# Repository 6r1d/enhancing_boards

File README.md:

# Enhancing boards

Hello! This is a place I will be pushing KiCad boards and documentation for those.
I am doing that to be able to show, discuss and improve those boards, also I want them to be useful for someone.

There are lots of ready boards for DIY enthusiasts, but I can't always find a well-tested layout made in open-source software, so there's always something to improve, too. :-)

## Plans
I am interested in electronic music synthesizers and single-board computers that can be used in those; I intend to test different microcontrollers and sound-related hardware. Besides that, I have a ton of breakout boards from China. I want reusable layouts for chips, so that's something I'll gradually clean up and add here, too.

Currently I'm waiting for a very primitive [ESP32-Wroom](https://www.espressif.com/sites/default/files/documentation/esp32-wroom-32_datasheet_en.pdf) boards to determine if 3.3V power is a minimal requirement.
If that's the case, I will add my own [ESP32](https://www.espressif.com/en/products/socs/esp32) board here.

### Interesting ICs
There are integrated circuits I really want to use later.

* [STM32F103C8T6](https://www.st.com/resource/en/datasheet/stm32f103c8.pdf) microcontroller, because Maple and Blue Pill were very nice until the clone boards with clone chips started popping up. New ones are really hard to distinguish visually!
* [Azoteq IQS263B](https://www.azoteq.com/product/iqs263b/) capacitive sensor IC, I²C interface. Allows to make capacitive wheels, sliders and buttons.
* [Azoteq IQS550-B000](https://www.azoteq.com/product/iqs550-b000/) capacitive sensor IC, 15 rows, 10 columns, 3584 x 2304 max resolution, I²C interface. Allows to make large capacitive sensor panels. **UPD**: I ordered the test kit from DigiKey and it is being delivered by USPS to Qwintry warehouse right now.
* [CAP1188](https://www.microchip.com/wwwproducts/en/CAP1188) capacitive sensor IC, 8 capacitive sensor inputs, I²C interface.
* [TXS0108E](https://www.ti.com/lit/ds/symlink/txs0108e.pdf) / YF08E and maybe other level converters, since I have those. (There is some concern about the fakes, too, because I saw very different labels for the same chip.)
* [SI4735](https://www.silabs.com/documents/public/data-sheets/Si4730-31-34-35-D60.pdf), radio receiver IC because it is tiny, works, and might be interesting to play with.

## Testing

When I can, I will test the boards using the toner-transfer method, adding a note about the results and fixing the boards. Otherwise, I'll order everything I can't make elsewhere.

If you want to do tests right now, **feel free to create an issue**! I will provide any additional info you'll want for toner-transfer method or I will help with factory Gerber.

## Current boards

| Directory                             | State                            | Description                                         |
| ------------------------------------- | -------------------------------- | --------------------------------------------------- |
| [PCM5102A](/PCM5102A)                 | UNTESTED                         | [PCM5102A](https://www.ti.com/product/PCM5102A) [I²S](https://en.wikipedia.org/wiki/I%C2%B2S) dac with [TPA6132A2](https://www.ti.com/product/TPA6132A2) headphone amp |
| [MIDI I/O](/MIDI_IO)                  | STABLE, tested for 5V | [MIDI](https://en.wikipedia.org/wiki/MIDI) [I/O](https://en.wikipedia.org/wiki/Input/output) board for 5V devices                       |
| [MCP4725 breakout](/MCP4725_breakout) | UNTESTED                         | [I²C](https://en.wikipedia.org/wiki/I%C2%B2C) [DAC](https://en.wikipedia.org/wiki/Digital-to-analog_converter) breakout board, 1 output                    |
| [MCP4728 breakout](/MCP4728_breakout) | UNTESTED                         | [I²C](https://en.wikipedia.org/wiki/I%C2%B2C) [DAC](https://en.wikipedia.org/wiki/Digital-to-analog_converter) breakout board, 4 outputs                   |
| [MUX_4067](/MUX_4067)                 | UNTESTED                         | 16-pin analog / digital [multiplexor](https://en.wikipedia.org/wiki/Multiplexer) breakout board  |

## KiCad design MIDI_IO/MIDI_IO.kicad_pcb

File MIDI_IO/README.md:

# MIDI I/O board

Assembled:

3D render:

[PCB photos](https://i.imgur.com/VaKc3Vo.jpg)

## Current state

I have five physical boards and each of those is working. Moreover, long-term tests are done.
I'm still concerned about the device speed and I want to perform 24 hour long tests on 5V and 3.3V devices, as well.

## Specifications

This board has two DIN-5 ports for input and output and [6N138](https://www.vishay.com/docs/83605/6n139.pdf) to isolate input signal. 6N138 optoisolators were bought [here](https://aliexpress.ru/item/32545548201.html?spm=a2g0s.9042311.0.0.264d33edC1LcYz) and were tested by me well.
I've bought my DIN-5 sockets [here](https://aliexpress.ru/item/32402564814.html) on AliExpress, which seems cheap enough.

It is inspired by the fact [AliExpress](http://aliexpress.com/) boards for [MIDI](https://en.wikipedia.org/wiki/MIDI) are not that good and I had to [solder a resistor](https://twitter.com/I_am_6r1d/status/1299311510662021120) straight onto the optocouple leads to make one work.

It uses `1k 100 mHz` [ferrite beads](https://article.murata.com/en-eu/article/basics-of-noise-countermeasures-lesson-4) for [EMI protection](https://en.wikipedia.org/wiki/Electromagnetic_interference), currently [ILBB-0603ER102V](https://static6.arrow.com/aropdfconversion/c4f424f1ec3f9ac2c3a4ec0c3df1e3ee2574f7a5/ilbb0603.pdf) by [Vishay](https://www.vishay.com/).

This board is designed in [KiCad 5.1.6](https://kicad-pcb.org/).
Issues and advices are welcome!

## Testing

I was concerned about the components overheating over a long-term use,
so I decided to "spam" a hardware synthesizer with MIDI messages to check how it behaves.

First test was relatively simple: random notes were sent to Casio Privia synthesizer on low volume for three hours when input voltage was 5v.
I did not notice any glitches in the process (no randomly changing instruments or velocity).
To perform the test, I have used Arduino Uno and Arduino Mega boards.

Then I did a similar test for ~15 minutes on STM32 board (Blue Pill) and ESP32-WROOM board, both sent 3.3 V input to the board.

I also monitored how the signal is received by checking available bytes on UART. I should do more extensive tests later.
I am mostly interested in sending lots of MIDI data from E-MU 0404 to a 3.3V device to understand how well it behaves.

## Components

### 5V mode

This board is initially intended for use with devices, which have 5V [logic level](https://en.wikipedia.org/wiki/Logic_level) like [Arduino](https://www.arduino.cc/)
and 3.3 V board should be different component-wise, not layout-wise.

Schematic contains correct and tested resistor values for 5V,
according to MIDI DIN electrical [specification](https://www.midi.org/specifications-old/item/midi-din-electrical-specification).

This specification doesn't clearly state a resistor value for 6n138 optoisolator, currently it is 220 Ω,
which works for hours in practice, but **should be optimized** later.
The resistor I'm speaking of is called `R4` on KiCad schematic. In MIDI DIN spec it's called `Rd`.
It influences `speed of bit switching` on the optoisolator side connected to `RX` pin and `the power consumption`.

### 3.3 V mode

I have sent and received data on both STM32 and ESP32 using the current design.
`R4` value was the same as in 5V version, i.e. 220 Ω, which might be too low for the task.
While it gives a high switching speed (apparently, I don't have an oscilloscope to check right now),
it is different from the recommended value range, too.

Further tests should adress that and I should test the board with more appropriate resistors.

There are many possible changes to make for 3.3V. Some require changing the layout, some don't.

 * [PJRC](http://web.archive.org/web/20201025215735/https://forum.pjrc.com/threads/45416-Base-Emitter-Resistor-for-6N139-on-MIDI-input) - physics of the process, fixes, 6n137 recommendation
 * [EE StackExchange](https://electronics.stackexchange.com/questions/165255/midi-in-many-circuits) - more on physics, TLP2361 and H11L1 recommendation, possible layout alteration
 * [Samplerbox](https://www.samplerbox.org/article/midiinwithrpi) - recommendations about Raspberry Pi usage, a combination of `R4` = 1k and `R5` = 10k. Comment tells it doesn't work, though.
 * [EE StackExchange](https://electronics.stackexchange.com/questions/288448/minimize-current-consulption-for-midi-input-circuit) topic about power consumption recommends another topology, clamping the output transistor with Schottky diode like `SD101`, `BAS70`, `RB751`
 * [EE StackExchange](https://electronics.stackexchange.com/questions/102884/how-to-calculate-exactly-resistors-values-of-opto-coupler) also has a topic on exact calculation for a pull-up resistor

The **simplest** would be to pick `R4` = 1k, `R5` = 10k and perform the tests between two boards.
"MIDI in many circuits" topic explains that R5 range should be between 4.7 kΩ and 10 kΩ.

## To-Do

- [x] Check contacts on physical DIN-5 sockets: both pins and sizes
- - **UPD**: sockets have arrived, testing soon
- - **UPD-2**: ordered the board, optocouples and diodes arrived, waiting for passive components
- [x] Finish compatibility with current [MIDI DIN electrical specification](https://www.midi.org/specifications/item/midi-din-electrical-specification)
- [x] Clean components up
- [x] Order a PCB
- [x] Assemble a PCB
- [x] Test 3V3 mode on STM32 with available resistors
- [x] Test 3V3 mode on ESP32-WROOM with available resistors
- [ ] Run a high-speed byte transfer through an optocouple and compare sent and received byte for a day
- [ ] Test connection reliability between two 3V3 devices both usin MIDI I/O board
- [ ] Test 3V3 mode for [Raspberry Pi](https://www.raspberrypi.org/), add a level shifter if it will be required. Look at [this article](https://openenergymonitor.org/forum-archive/node/12412.html) if things start to break.

## Credits

* [KiCad](https://kicad-pcb.org/) 3d Packages and library by Walter Lain (`kcswalter` at `member.fsf.org`), downloaded at [Smisioto.No-IP.org](http://smisioto.no-ip.org/elettronica/kicad/kicad-en.htm)

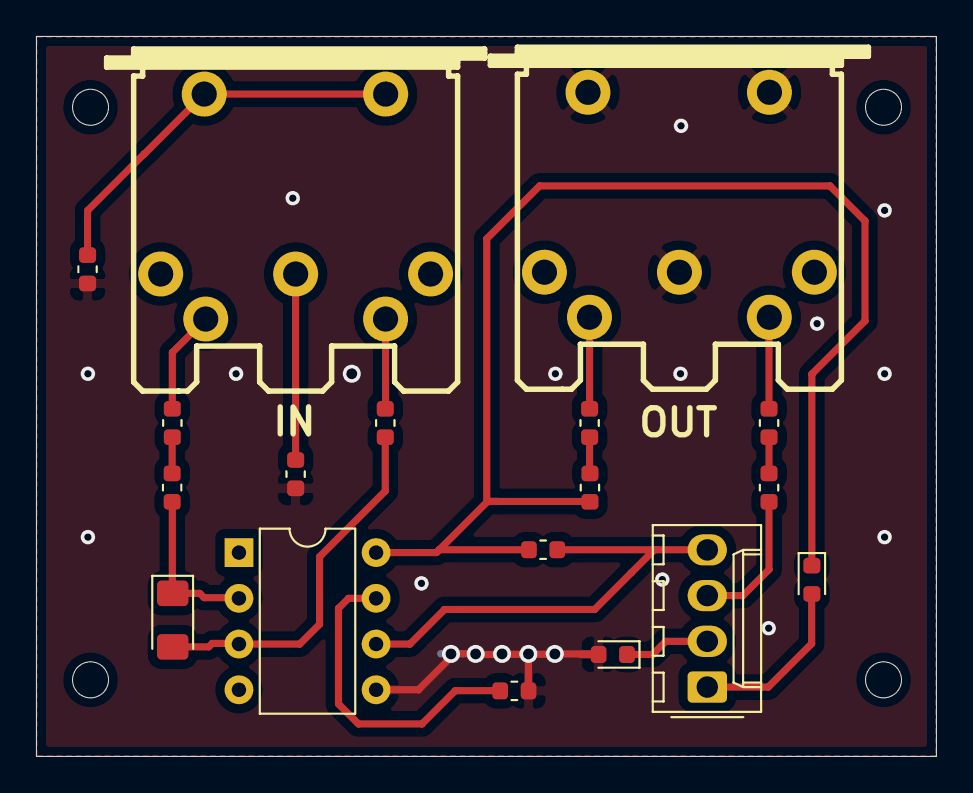
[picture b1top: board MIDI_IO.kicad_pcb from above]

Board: 2 copper layers, 50.0 x 40.0 mm, 23 parts (1 on the bottom side), 18 nets.

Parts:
C1, C2: 0.1uF; C_0603_1608Metric
D1: 1N914; D_1206_3216Metric_Pad1.42x1.75mm_HandSolder
D2, D3: D; D_0603_1608Metric
FB1, FB2, FB3, FB4: 1k 100mHz; L_0603_1608Metric
H1, H2, H3, H4: MountingHole_Pad; MountingHole_2mm
J1: Conn_01x04; Molex_KK-254_AE-6410-04A_1x04_P2.54mm_Vertical
J_IN_1: DIN-5_180degree_JS; din-5-shielded
J_OUT_1: DIN-5_180degree_JS; din-5-shielded
R1, R2, R3, R4: 220; R_0603_1608Metric
R5: 4.7k; R_0603_1608Metric
U1: 6N138; DIP-8_W7.62mm
svg2mod: G***; Grid_logo

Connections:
+5V: D2.1, R2.1, R4.1, U1.8
GND: C1.2, C2.2, D3.2, J_OUT_1.2, J_OUT_1.6, R5.2, U1.5
IN_SH: C1.1, J_IN_1.2
IN_SH_OUT: C2.1, J_IN_1.6
unnamed: D1.1, R3.1, U1.2
unnamed: D1.2, FB4.1, U1.3
unnamed: D2.2, J1.1
unnamed: D3.1, J1.2
unnamed: FB1.1, J_OUT_1.5
unnamed: FB1.2, R1.1
unnamed: FB2.1, R2.2
unnamed: FB2.2, J_OUT_1.4
unnamed: FB3.1, R3.2
unnamed: FB3.2, J_IN_1.4
unnamed: FB4.2, J_IN_1.5
unnamed: R5.1, U1.7
RX: J1.4, R4.2, U1.6
TX: J1.3, R1.2

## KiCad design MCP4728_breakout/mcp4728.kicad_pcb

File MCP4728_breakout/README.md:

# MCP4728 breakout board

## Idea

This breakout board has 4 DAC ports, controlled by I²C protocol. It is based on the default schematic from `MCP4728` datasheet and Adafruit breakout board.

**Attention!** Output voltage will depend on the input! To imagine how that works, let's say you have a 5V source. Integer you are sending using I²C varies from 0 to 4095. Now, when you have 5V input and 4095 on I²C, you'll have 5V on the output. If you set 0 on I²C, you'll get zero voltage. But you can put any value between 0 and 4095, too, getting all possible in-between voltages. Same goes for 3.3V.

It is currently untested, but the board seems simple enough so there should be no errors.

## Documents

[Datasheet](https://ww1.microchip.com/downloads/en/DeviceDoc/22187E.pdf)

## Links

* [Adafruit breakout board](https://learn.adafruit.com/adafruit-mcp4728-i2c-quad-dac/downloads) documentation

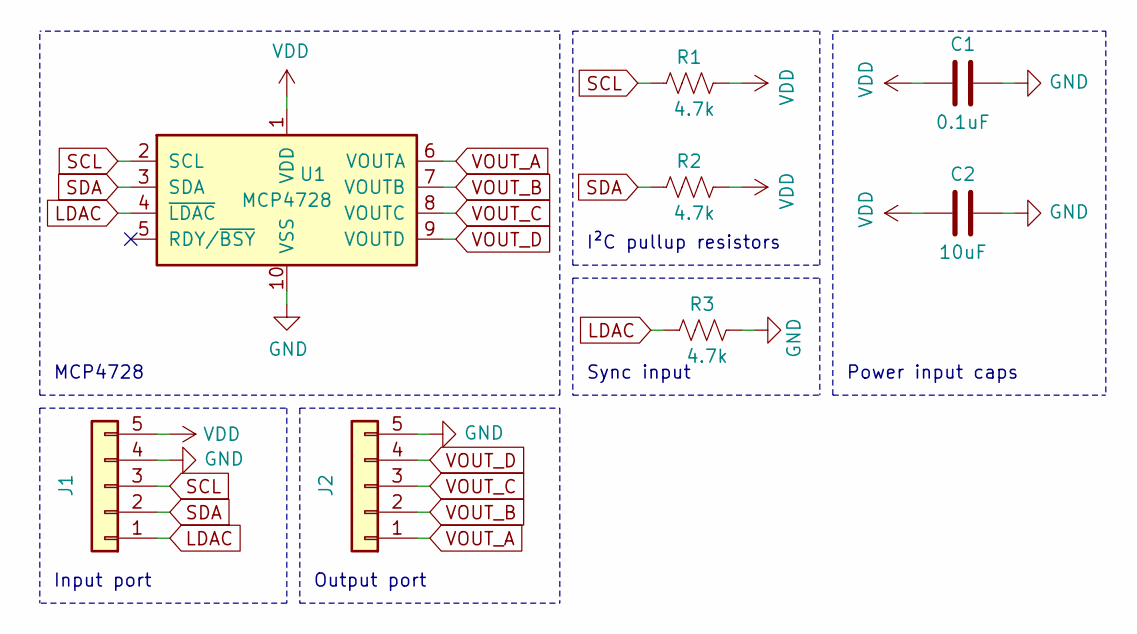
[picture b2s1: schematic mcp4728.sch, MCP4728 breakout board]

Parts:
C1: 0.1uF; C_0603_1608Metric
C2: 10uF; C_0603_1608Metric
J1, J2: Conn_01x05; PinHeader_1x05_P2.54mm_Vertical
R1, R2, R3: 4.7k; R_0603_1608Metric
U1: MCP4728; MSOP-10_3x3mm_P0.5mm

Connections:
GND: C1.1, C2.1, J1.4, J2.5, R3.2, U1.10 (VSS)
LDAC: J1.1, R3.1, U1.4 (~LDAC)
SCL: J1.3, R1.1, U1.2 (SCL)
SDA: J1.2, R2.1, U1.3 (SDA)
VDD: C1.2, C2.2, J1.5, R1.2, R2.2, U1.1 (VDD)
VOUT_A: J2.1, U1.6 (VOUTA)
VOUT_B: J2.2, U1.7 (VOUTB)
VOUT_C: J2.3, U1.8 (VOUTC)
VOUT_D: J2.4, U1.9 (VOUTD)

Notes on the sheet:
MCP4728
I²C pullup resistors
Input port
Output port
Power input caps
Sync input

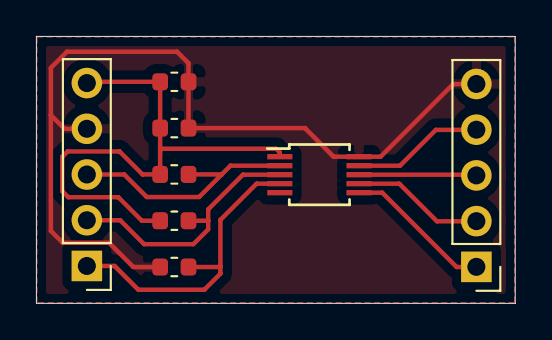
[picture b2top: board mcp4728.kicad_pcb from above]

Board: 2 copper layers, 26.6 x 14.8 mm, 8 parts (0 on the bottom side), 9 nets.

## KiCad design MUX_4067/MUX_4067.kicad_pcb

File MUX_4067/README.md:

# 16-pin analog / digital multiplexor breakout board

## Idea

If you have never used multiplexors, this IC connects a single pin to **one of** the several outputs, where an output pin is picked using **other** digital input pins. Think [railroad switch](https://en.wikipedia.org/wiki/Railroad_switch), but for electronics, not for railroad.

I had some of those mux board around for quite some time and they are working nicely with Arduino, so I decided to make a copy of a very short schematic and to make my own layout. Why? Well, as usual, to test and be sure I can use them in my own devices later.

## Documentation

[Datasheet](https://www.ti.com/lit/ds/symlink/cd74hc4067.pdf)

## To-Do

- [ ] Use a multimeter's continuity testing on the original to ensure I'm using correct pins
- [ ] Order a board prototype
- [ ] Do a bunch of tests to determine it's not worse than normal breakout boards
- [ ] Create a 8-pin layout

## Links

* [SparkFun breakout board](http://cdn.sparkfun.com/datasheets/BreakoutBoards/Analog-Digital-Mux-Breakout-v11.pdf)
* [Arduino code for interacting with Mux](https://www.codrey.com/arduino-projects/analog-multiplexer-demultiplexer-primer/)

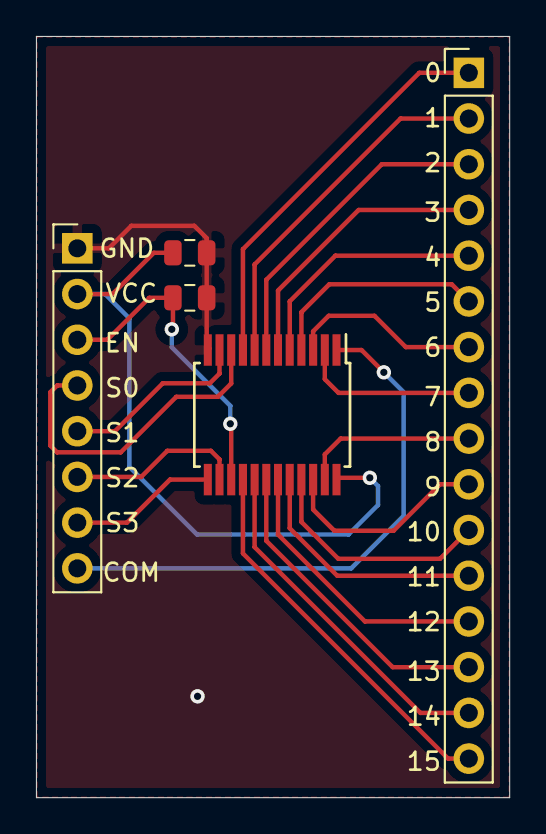
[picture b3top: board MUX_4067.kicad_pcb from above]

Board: 2 copper layers, 26.3 x 42.3 mm, 5 parts (0 on the bottom side), 24 nets.

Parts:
C1: 0.1uF; C_0805_2012Metric
J1: Conn_01x08; PinHeader_1x08_P2.54mm_Vertical
J2: Conn_01x16; PinHeader_1x16_P2.54mm_Vertical
R1: 10k; R_0805_2012Metric
U1: CD74HC4067SM; SSOP-24_5.3x8.2mm_P0.65mm

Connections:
COM: J1.8, U1.1
EN: J1.3, R1.1, U1.15
GND: C1.2, J1.1, R1.2, U1.12
unnamed: J2.1, U1.9
unnamed: J2.2, U1.8
unnamed: J2.3, U1.7
unnamed: J2.4, U1.6
unnamed: J2.5, U1.5
unnamed: J2.6, U1.4
unnamed: J2.7, U1.3
unnamed: J2.8, U1.2
unnamed: J2.9, U1.23
unnamed: J2.10, U1.22
unnamed: J2.11, U1.21
unnamed: J2.12, U1.20
unnamed: J2.13, U1.19
unnamed: J2.14, U1.18
unnamed: J2.15, U1.17
unnamed: J2.16, U1.16
S0: J1.4, U1.10
S1: J1.5, U1.11
S2: J1.6, U1.14
S3: J1.7, U1.13
VCC: C1.1, J1.2, U1.24

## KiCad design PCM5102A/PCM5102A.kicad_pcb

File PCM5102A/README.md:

# PCM 5102A interface for Raspberry PI

This board essentially consists of a [PCM5102A DAC](https://www.ti.com/lit/ds/symlink/pcm5102a.pdf) and [TPA6132A2 amplifier](https://www.ti.com/lit/ds/symlink/tpa6132a2.pdf) ICs.

[PCM5102A](https://www.ti.com/lit/ds/symlink/pcm5102a.pdf) IC is used in [PLL operation](https://en.wikipedia.org/wiki/Phase-locked_loop) schematic.
It means [SCK pin](https://hackaday.com/2019/04/18/all-you-need-to-know-about-i2s/) is not used and frequency generation happens internally, using phase-locked loop control system.
According to the datasheed, this configuration is not in any way bad and even slightly reduces [electromagnetic interference](https://en.wikipedia.org/wiki/Electromagnetic_interference).
I am using PCM5102A because it has high sound quality and mute circuitry.
Also, I ordered a board with this chip to test with Raspberry Pi before starting my own one.

I added [TPA6132A2](https://www.ti.com/lit/ds/symlink/tpa6132a2.pdf) headphone amplifier to isolate DAC from other devices.
It is used in a single-ended input signal mode. I have concerns about damaging the DAC with short circuit, so that's why there's a tiny amplifier IC.

Current 2-ldo schematic is inspired by ["GY" board from AliExpress](https://i.stack.imgur.com/ZBK8Q.jpg).
I got a working one at [WavGat store](https://aliexpress.ru/item/33001714060.html).

There are also 3-ldo versions of the same schematic by AiDiy.cc.
I guess it has a separate digital, analog and charge pump LDO, and it's a well-known [AMS-1117-3.3](http://www.advanced-monolithic.com/pdf/ds1117.pdf), at that!
It will be nice to test if there is any difference in sound later.

This board is designed in [KiCad 5.1.6](https://kicad-pcb.org/). It has 5V input voltage and 3.3V I²S voltage. Issues and advices are welcome!

## Progress

* I checked schematic using two datasheets paying as much attention as I can. It is still possible to encounter some issues and I haven't tested the board design yet.
* I found out my `5V` label is not related to the signal. RaspberryPi signal level is 3.3V. Changes are not required, since board is based on a design, tested with RaspberryPi.

## To-Do

- [ ] Do a [toner-transfer method](https://hackaday.com/2016/09/12/take-your-pcbs-from-good-to-great-toner-transfer/) test
- [ ] Test with [jumpers](https://en.wikipedia.org/wiki/Jumper_(computing))
- [ ] Remove excess power wiring from the layout
- [ ] Do a second toner-transfer method test board
- [ ] Add labels on the board to mark inputs and outputs
- [ ] Order a test batch at [PCBWay](https://www.pcbway.com/) / [JLCPCB](http://jlcpcb.com/) / etc.
- [ ] Add labels after the best board layout is established
- [ ] It will be nice to have optocouples to control the DAC and AMP mute circuitry after the prototype is working. (Analyze ChipDip mute circuit below)
- [ ] It will be interesting to test 1 and 3 LDO configuration later. It seems the datasheet relies on one LDO, while AiDiy schematic relies on three.
- [ ] Add a MUTE pin controlling optocouples for DAC and AMP ICs

UPD: TPA6132 breakout board is here, so I can test it before I do toner-transfer. Sep 10, 2020.

## Datasheets

* [DAC datasheet](https://www.ti.com/lit/ds/symlink/pcm5102a.pdf)
* [AMP datasheet](https://www.ti.com/lit/ds/symlink/tpa6132a2.pdf)

## Other links

* [StackOverflow](https://raspberrypi.stackexchange.com/questions/76188/how-to-make-pcm5102-dac-work-on-raspberry-pi-zerow) question inspiring me to use the initial board
* [Player.ru](http://player.ru/showthread.php?t=188998&page=207) - Hi-Res chinese board photos by maxkur, jumper pads configuration info (page 207)
* [Goldilocks Analogue schematic](https://feilipu.files.wordpress.com/2014/04/goldilocksanaloguedacamplifiers.png), which inspired me to use TPA6132A2 amp.
* [ChipDip.ru circuit](https://static.chipdip.ru/lib/335/DOC004335833.pdf) has an interesting XSMT connection for debouncing mute signal

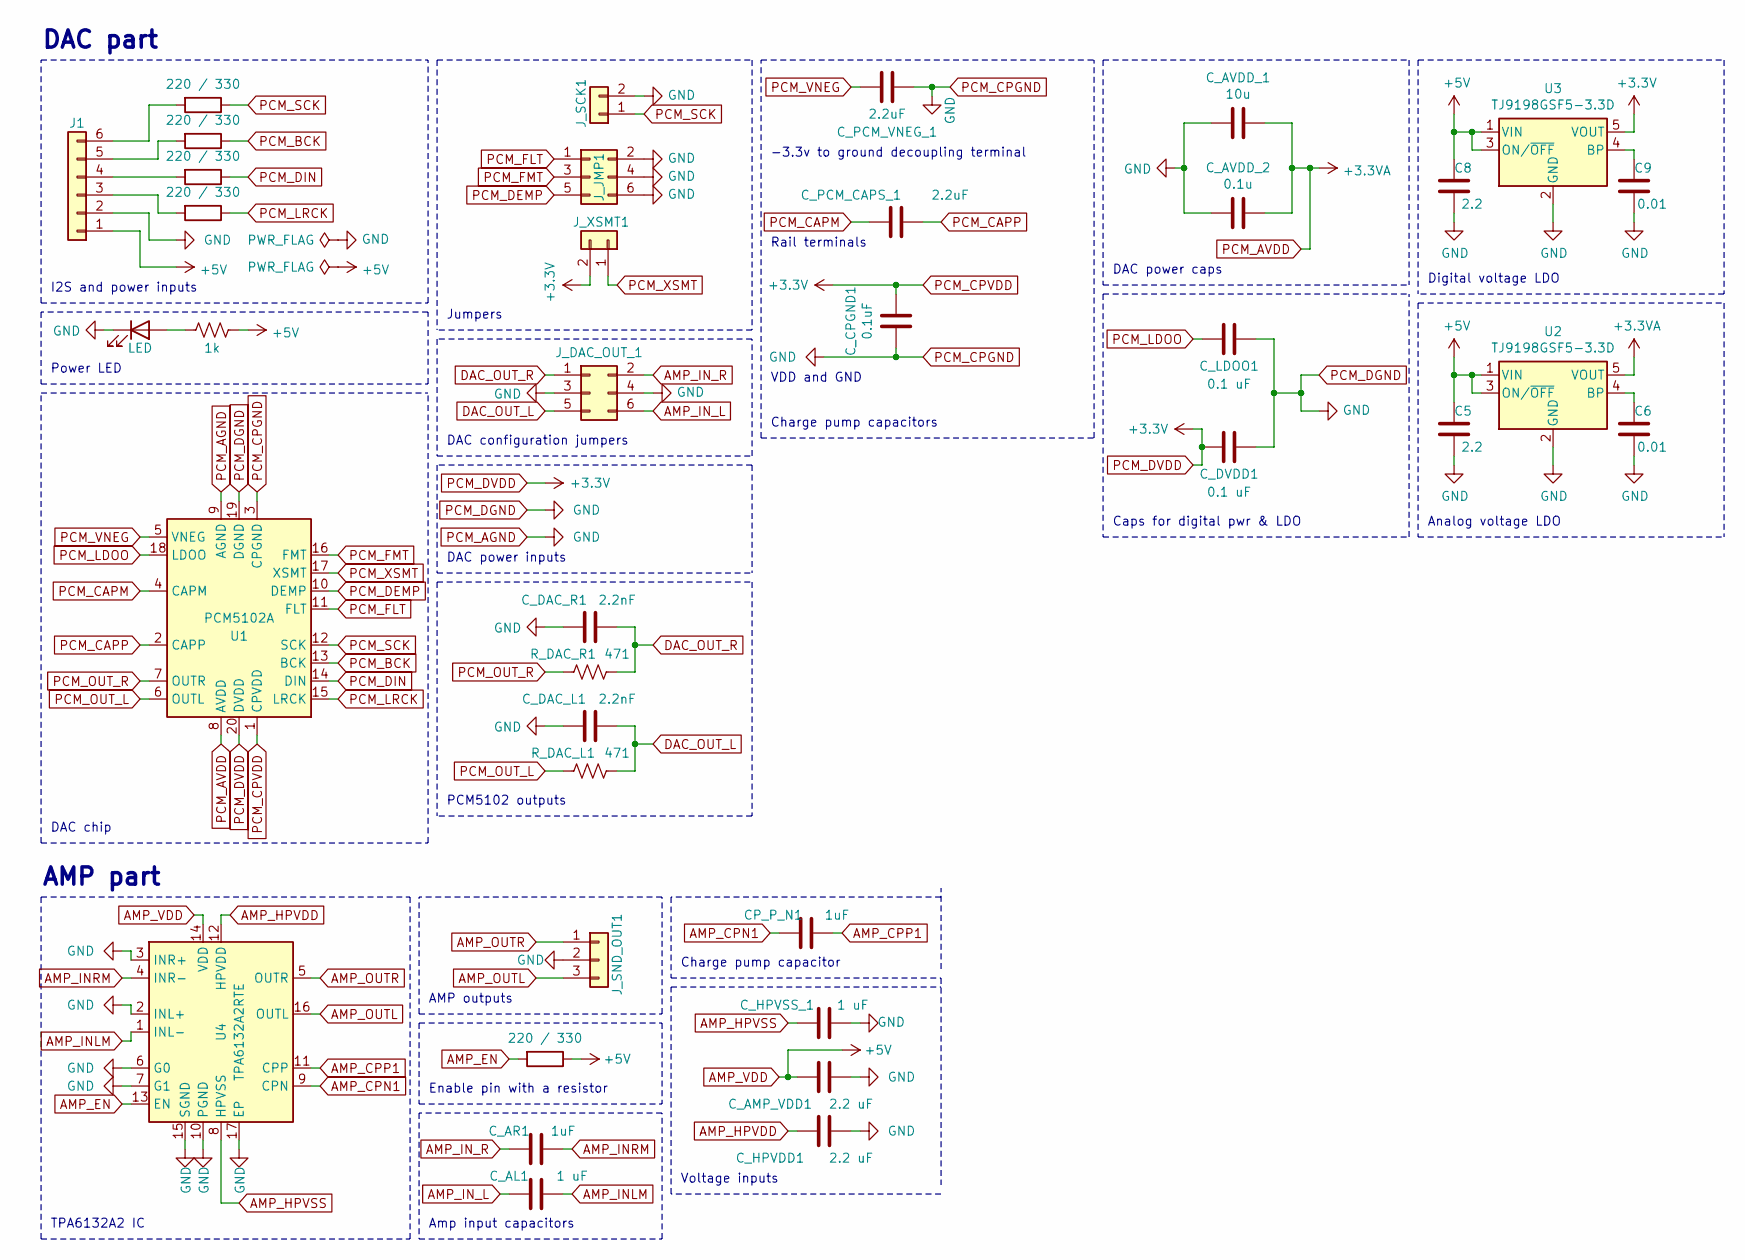
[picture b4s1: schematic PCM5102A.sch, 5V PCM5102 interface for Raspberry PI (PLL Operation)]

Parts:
C5, C8: 2.2; C_0603_1608Metric
C6, C9: 0.01; C_0603_1608Metric
CP_P_N1: 1uF; C_0603_1608Metric
C_AL1: 1 uF; C_0603_1608Metric
C_AMP_VDD1: 2.2 uF; C_0603_1608Metric
C_AR1: 1uF; C_0603_1608Metric
C_AVDD_1: 10u; C_0603_1608Metric
C_AVDD_2: 0.1u; C_0603_1608Metric
C_CPGND1: 0.1uF; C_0603_1608Metric
C_DAC_L1: 2.2nF; C_0603_1608Metric
C_DAC_R1: 2.2nF; C_0603_1608Metric
C_DVDD1: 0.1 uF; C_0603_1608Metric
C_HPVDD1: 2.2 uF; C_0603_1608Metric
C_HPVSS_1: 1 uF; C_0603_1608Metric
C_LDOO1: 0.1 uF; C_0603_1608Metric
C_PCM_CAPS_1: 2.2uF; C_0603_1608Metric
C_PCM_VNEG_1: 2.2uF; C_0603_1608Metric
D1: LED; LED_0603_1608Metric_Castellated
J1: Conn_01x06; PinHeader_1x06_P2.54mm_Vertical
J_DAC_OUT_1: Conn_02x03_Odd_Even; PinHeader_2x03_P2.54mm_Vertical
J_JMP1: Conn_02x03_Odd_Even; PinHeader_2x03_P2.54mm_Vertical
J_SCK1: Conn_01x02; PinHeader_1x02_P2.54mm_Vertical
J_SND_OUT1: Conn_01x03; PinHeader_1x03_P2.54mm_Vertical
J_XSMT1: Conn_01x02; PinHeader_1x02_P2.54mm_Vertical
R_AMP_EN_2: 220 / 330; R_0603_1608Metric
R_BCK_1: 220 / 330; R_0603_1608Metric
R_DAC_L1: 471; R_0603_1608Metric
R_DAC_R1: 471; R_0603_1608Metric
R_DIN_1: 220 / 330; R_0603_1608Metric
R_LCK_1: 220 / 330; R_0603_1608Metric
R_LED1: 1k; R_0603_1608Metric
R_SCK_1: 220 / 330; R_0603_1608Metric
U1: PCM5102A; TSSOP-20_4.4x6.5mm_P0.65mm
U2, U3: TJ9198GSF5-3.3D; SOT-23-5
U4: TPA6132A2RTE; WQFN-16-1EP_3x3mm_P0.5mm_EP1.6x1.6mm_ThermalVias

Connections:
AMP_CPN1: CP_P_N1.2, U4.9 (CPN)
AMP_CPP1: CP_P_N1.1, U4.11 (CPP)
AMP_EN: R_AMP_EN_2.2, U4.13 (EN)
AMP_HPVDD: C_HPVDD1.1, U4.12 (HPVDD)
AMP_HPVSS: C_HPVSS_1.1, U4.8 (HPVSS)
AMP_INLM: C_AL1.2, U4.1 (INL-)
AMP_INRM: C_AR1.2, U4.4 (INR-)
AMP_IN_L: C_AL1.1, J_DAC_OUT_1.6
AMP_IN_R: C_AR1.1, J_DAC_OUT_1.2
AMP_OUTL: J_SND_OUT1.3, U4.16 (OUTL)
AMP_OUTR: J_SND_OUT1.1, U4.5 (OUTR)
AMP_VDD: C5.2, C8.2, C_AMP_VDD1.1, J1.1, R_AMP_EN_2.1, R_LED1.1, U2.1 (VIN), U2.3 (ON/~OFF~), U3.1 (VIN), U3.3 (ON/~OFF~), U4.14 (VDD)
DAC_OUT_L: C_DAC_L1.1, J_DAC_OUT_1.5, R_DAC_L1.1
DAC_OUT_R: C_DAC_R1.2, J_DAC_OUT_1.1, R_DAC_R1.1
unnamed: C6.2, U2.4 (BP)
unnamed: C9.2, U3.4 (BP)
unnamed: D1.2 (A), R_LED1.2
unnamed: J1.3, R_LCK_1.2
unnamed: J1.4, R_DIN_1.2
unnamed: J1.5, R_BCK_1.2
unnamed: J1.6, R_SCK_1.2
PCM_AGND: C5.1, C6.1, C8.1, C9.1, C_AMP_VDD1.2, C_AVDD_1.2, C_AVDD_2.2, C_CPGND1.2, C_DAC_L1.2, C_DAC_R1.1, C_DVDD1.1, C_HPVDD1.2, C_HPVSS_1.2, C_LDOO1.2, C_PCM_VNEG_1.1, D1.1 (K), J1.2, J_DAC_OUT_1.3, J_DAC_OUT_1.4, J_JMP1.2, J_JMP1.4, J_JMP1.6, J_SCK1.2, J_SND_OUT1.2, U1.3 (CPGND), U1.9 (AGND), U1.19 (DGND), U2.2 (GND), U3.2 (GND), U4.2 (INL+), U4.3 (INR+), U4.6 (G0), U4.7 (G1), U4.10 (PGND), U4.15 (SGND), U4.17 (EP)
PCM_AVDD: C_AVDD_1.1, C_AVDD_2.1, U1.8 (AVDD), U2.5 (VOUT)
PCM_BCK: R_BCK_1.1, U1.13 (BCK)
PCM_CAPM: C_PCM_CAPS_1.2, U1.4 (CAPM)
PCM_CAPP: C_PCM_CAPS_1.1, U1.2 (CAPP)
PCM_CPVDD: C_CPGND1.1, C_DVDD1.2, J_XSMT1.2, U1.1 (CPVDD), U1.20 (DVDD), U3.5 (VOUT)
PCM_DEMP: J_JMP1.5, U1.10 (DEMP)
PCM_DIN: R_DIN_1.1, U1.14 (DIN)
PCM_FLT: J_JMP1.1, U1.11 (FLT)
PCM_FMT: J_JMP1.3, U1.16 (FMT)
PCM_LDOO: C_LDOO1.1, U1.18 (LDOO)
PCM_LRCK: R_LCK_1.1, U1.15 (LRCK)
PCM_OUT_L: R_DAC_L1.2, U1.6 (OUTL)
PCM_OUT_R: R_DAC_R1.2, U1.7 (OUTR)
PCM_SCK: J_SCK1.1, R_SCK_1.1, U1.12 (SCK)
PCM_VNEG: C_PCM_VNEG_1.2, U1.5 (VNEG)
PCM_XSMT: J_XSMT1.1, U1.17 (XSMT)

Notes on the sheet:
I2S and power inputs
Power LED
PCM5102 outputs
Digital voltage LDO
Analog voltage LDO
Jumpers
Caps for digital pwr & LDO
AMP outputs
Enable pin with a resistor
Voltage inputs
Amp input capacitors
Charge pump capacitor
TPA6132A2 IC
Charge pump capacitors
DAC configuration jumpers
DAC power inputs
DAC power caps
DAC part
AMP part
DAC chip
Rail terminals
-3.3v to ground decoupling terminal
VDD and GND

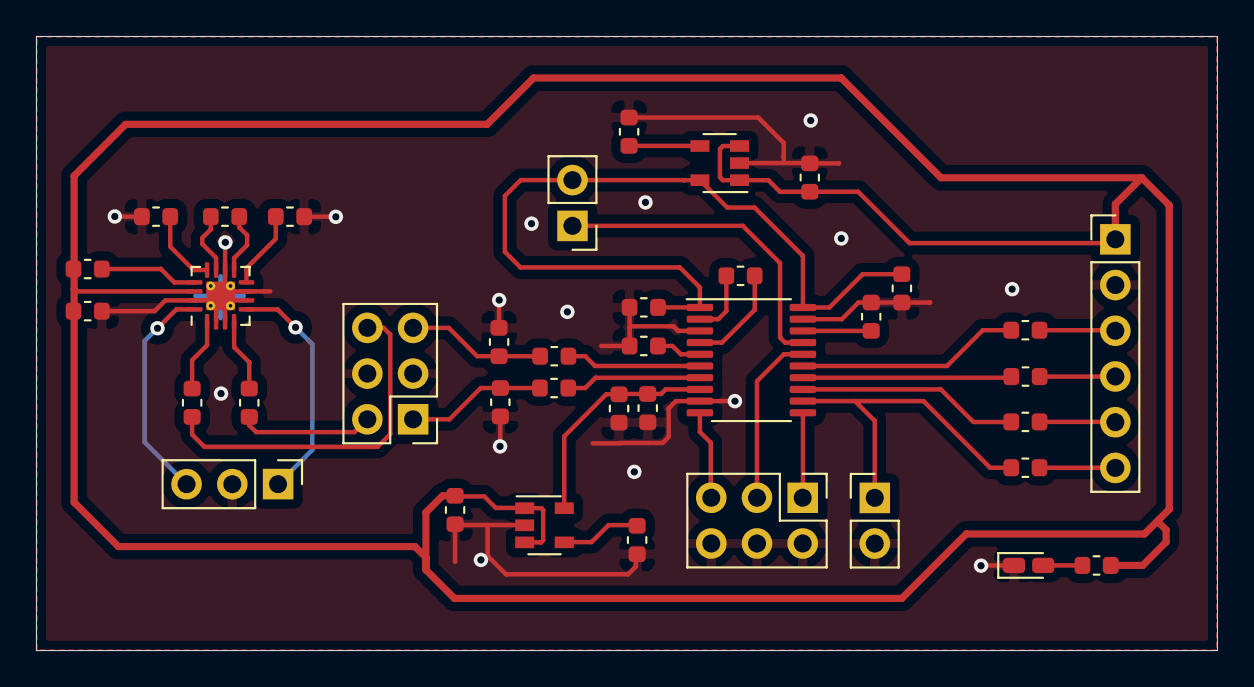
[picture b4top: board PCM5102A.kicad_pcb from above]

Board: 2 copper layers, 65.6 x 34.1 mm, 38 parts (0 on the bottom side), 38 nets.

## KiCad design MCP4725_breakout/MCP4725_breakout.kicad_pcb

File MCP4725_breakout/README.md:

# MCP4725 breakout board

## Idea

I have a couple MCP4725 boards and I decided I want to copy the layout to [KiCad](https://kicad-pcb.org/) so it's easy to use later in some [CV/Gate](https://en.wikipedia.org/wiki/CV/gate) interface for music production, volume control for an amplifier and so on. Those worked for me in Arduino, giving a stable amount of voltage.

**Attention!** Output voltage will depend on the input! To imagine how that works, let's say you have a 5V source. Integer you are sending using I²C varies from 0 to 4095 (12-bit). Now, when you have 5V input and 4095 on I²C, you'll have 5V on the output. If you set 0 on I²C, you'll get zero voltage. But you can put any value between 0 and 4095, too, getting all possible in-between voltages. Same goes for 3.3V.

## Notes

MCP4725 chip works with both 3.3V and 5V input. It uses I²C interface to operate and needs `SCL` and `SDA` pins to communicate.
There is a library I used by Adafruit and I added it to the links.

When I used the chip, I found out there are several chip models and I²C address depends on the model and A0 pin, which might be useful to know.
SMD resistor on a jumper pad was marked `103`, so I'd say it's 10 kOhm resistor. Testing a real-life breakout board using Mastech MY-68 multimeter shows `10.03 kOhm`, which is close enough.

`SDA` and `SCL` resistors are marked as `472`, so I think those are 4.7 kOhm resistors.
Testing a real-life breakout board with a Mastech MY-68 multimeter shows `4.64 kOhms`, which is close enough, too.

This board is designed in [KiCad 5.1.6](https://kicad-pcb.org/). Issues and advices are welcome!

### Connection

#### Arduino Uno / Nano

| Arduino pin    | DAC board pin |
| -------------- | ------------- |
| `5V` / `3.3V`  | `VCC`         |
| `GND`          | `GND`         |
| `A4`           | `SDA`         |
| `A5`           | `SCL`         |

### Addresses

There are several possible address value for MCP4725 chip.
Those depend on exact chip type and on `A0` pin, which can be tied to `Vss` or `Vdd`.

I found addresses in [I²C devices](https://i2cdevices.org/) site and Adafruit demo.
My board from AliExpress had `0x60` address.

| Part number | A0 state      | Addr (hex) | Checked |
| ----------- | ------------- | ---------- | ------- |
| MCP4725A0   | default / GND | 0x60       | &#9745; |
| MCP4725A0   | VCC           | 0x61       | &#9745; |
| MCP4725A1   | default / GND | 0x62       | &#9744; |
| MCP4725A1   | VCC           | 0x63       | &#9744; |
| MCP4725A2   | default / GND | 0x64       | &#9744; |
| MCP4725A2   | VCC           | 0x65       | &#9744; |
| MCP4725A3   | default / GND | 0x66       | &#9744; |
| MCP4725A3   | VCC           | 0x67       | &#9744; |

### Case labels

It might be interesting to know that chips are packed in 6-Lead `SOT-23` case which has a label on it.
So, if you see `AJ25` label, your part is `MCP4725A0`.

| Part number     | Option | Addresses  |
| --------------- | ------ | ---------- |
| MCP4725A0       | AJ NN  | 0x60, 0x61 |
| MCP4725A1       | AP NN  | 0x62, 0x63 |
| MCP4725A2       | AQ NN  | 0x64, 0x65 |
| MCP4725A3       | AR NN  | 0x66, 0x67 |

## Documentation

[MCP4725 Datasheet](http://ww1.microchip.com/downloads/en/DeviceDoc/22039d.pdf)

## Links

* [Adafruit library](https://github.com/adafruit/Adafruit_MCP4725)
* [Adafruit tutorial](https://learn.adafruit.com/mcp4725-12-bit-dac-tutorial?view=all)
* [SparkFun](https://www.sparkfun.com/products/12918) breakout board
* [EasyEDA version to compare the layout later](https://easyeda.com/alexander.burykin/I2C_DAC_Breakout_MCP4725_Open_hardware-91xPJ1jBu) by [Alexander Burykin](https://easyeda.com/alexander.burykin)
* [EasyEDA layout](https://easyeda.com/editor#id=e36a5e46d0c54cee9079e0bdedf030fe)
* [LCSC components](https://lcsc.com/search?q=MCP4725) to see the current price range. Currently it is around $1 and more for quantities less than 10, can be as low as $0.6 in large quantities.
* [Additional documentation on MCP4725](https://micro-pi.ru/mcp4725-%D1%86%D0%B8%D1%84%D1%80%D0%BE-%D0%B0%D0%BD%D0%B0%D0%BB%D0%BE%D0%B3%D0%BE%D0%B2%D1%8B%D0%B9-%D0%BF%D1%80%D0%B5%D0%BE%D0%B1%D1%80%D0%B0%D0%B7%D0%BE%D0%B2%D0%B0%D1%82%D0%B5%D0%BB%D1%8C/) (russian)

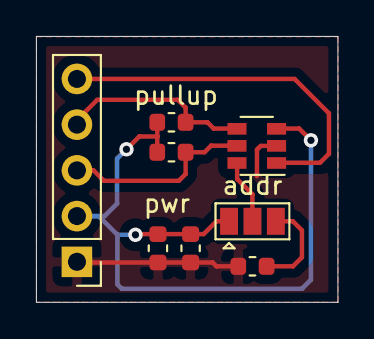
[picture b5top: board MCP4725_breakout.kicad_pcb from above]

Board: 2 copper layers, 16.7 x 14.8 mm, 8 parts (0 on the bottom side), 7 nets.

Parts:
C1: 10uF; C_0603_1608Metric
C2: 0.1uF; C_0603_1608Metric
J1: Conn_01x05; PinHeader_1x05_P2.54mm_Vertical
J2: Conn_01x03; SolderJumper-3_P1.3mm_Open_Pad1.0x1.5mm
R1, R2: 4.7k; R_0603_1608Metric
R3: 10k; R_0603_1608Metric
U1: MCP4725; SOT-23-6

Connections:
A0_0: J2.2, U1.6
unnamed: J2.3, R3.1
OUT_0: J1.5, U1.1
SCL_0: J1.3, R1.1, U1.5
SDA_0: J1.4, R2.2, U1.4
VDD: C1.1, C2.1, J1.2, J2.1, R1.2, R2.1, U1.3
VSS: C1.2, C2.2, J1.1, R3.2, U1.2

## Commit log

2020-09-01 Adds PCM5102A board
2020-09-01 Updates PCM5102A board documentation
2020-09-01 Adds MIDI IO board
2020-09-01 Improves documentation 😎
2020-09-01 Adds MCP4725 breakout board
2020-09-01 Adds a 16-channel TI mux board
2020-09-01 Updates for MUX_4067 documentation
2020-09-01 Updates README
2020-09-02 Adds a MCP4728 breakout board
2020-09-10 Updates MIDI IO board
2020-09-10 Fixes naming for MIDI IO board
2020-09-10 Improves MIDI shield
2020-09-10 Little doc update for PCM5102A
2020-09-14 Updates MIDI-IO board to a last state
2020-09-14 Updates docs for MIDI-IO board
2020-10-14 Adds a MIDI IO board photo, updates documentation
2020-10-24 Adds photos for MIDI IO board (assembled)
2020-10-26 Updates README for MIDI IO after initial tests
